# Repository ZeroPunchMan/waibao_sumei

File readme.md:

# 协议说明
校验计算方式: 类型字段和数据字段之和

## 开始或暂停
APP下发:
| 包头  | 方向  | 令牌  | 长度  | 类型  |        数据        | 校验  |
| :---: | :---: | :---: | :---: | :---: | :----------------: | :---: |
| 0xae  | 0x01  | 0xf0  | 0x02  | 0x01  | [0]: 0-暂停;1-开始; | 校验  |

设备回复
| 包头  | 方向  | 令牌  | 长度  | 类型  |        数据        | 校验  |
| :---: | :---: | :---: | :---: | :---: | :----------------: | :---: |
| 0xae  | 0x02  | 0xf0  | 0x02  | 0x01  | [0]: 0-暂停;1-开始;2-电池电量低;3-接入外部电源 | 校验  |

```
开启输出,APP下发内容:
ae 01 f0 02 01 01 02
设备收到后,回复内容:
ae 02 f0 02 01 01 02

如果电池电量低,回复内容:
ae 02 f0 02 01 02 03  
如果接入外部电源,回复内容:
ae 02 f0 02 01 03 04 
```
```
暂停输出,APP下发内容:
ae 01 f0 02 01 00 01
设备收到后,回复内容:
ae 02 f0 02 01 00 01 
```

## 紧急停止
APP下发:
| 包头  | 方向  | 令牌  | 长度  | 类型  | 数据  | 校验  |
| :---: | :---: | :---: | :---: | :---: | :---: | :---: |
| 0xae  | 0x01  | 0xf0  | 0x01  | 0x03  |  无   | 校验  |

设备回复
| 包头  | 方向  | 令牌  | 长度  | 类型  | 数据  | 校验  |
| :---: | :---: | :---: | :---: | :---: | :---: | :---: |
| 0xae  | 0x02  | 0xf0  | 0x01  | 0x03  |  无   | 校验  |

```
紧急停止,APP下发内容:
ae 01 f0 01 03 03
设备收到后,回复内容:
ae 02 f0 01 03 03 
```

## 设置输出
APP下发:
| 包头  | 方向  | 令牌  | 长度  | 类型  |                                                                                      数据                                                                                       | 校验  |
| :---: | :---: | :---: | :---: | :---: | :-----------------------------------------------------------------------------------------------------------------------------------------------------------------------------: | :---: |
| 0xae  | 0x01  | 0xf0  | 0x09  | 0x04  | [0]:手臂电机强度<br> [1]:手臂电机频率<br> [2]:胸部电机强度<br> [3]:胸部电机频率<br> [4]:背面上电机强度<br> [5]:背面上电机频率<br> [6]:背面下电机强度<br> [7]:背面下电机频率<br> | 校验  |

设备回复
| 包头  | 方向  | 令牌  | 长度  | 类型  |                                                                                      数据                                                                                       | 校验  |
| :---: | :---: | :---: | :---: | :---: | :-----------------------------------------------------------------------------------------------------------------------------------------------------------------------------: | :---: |
| 0xae  | 0x02  | 0xf0  | 0x09  | 0x04  | [0]:手臂电机强度<br> [1]:手臂电机频率<br> [2]:胸部电机强度<br> [3]:胸部电机频率<br> [4]:背面上电机强度<br> [5]:背面上电机频率<br> [6]:背面下电机强度<br> [7]:背面下电机频率<br> | 校验  |

```
举例
设置 手臂强度10 频率6; 胸部强度20 频率7; 背面上强度30 频率8; 背面下强度40 频率9; APP下发内容:
ae 01 f0 09 04 0a 06 14 07 1e 08 28 09 86
设备收到后,回复内容:
ae 02 f0 09 04 0a 06 14 07 1e 08 28 09 86 
```

## 电池上报
设备间隔2秒上报电量和电池状态
| 包头  | 方向  | 令牌  | 长度  | 类型  | 数据  | 校验  |
| :---: | :---: | :---: | :---: | :---: | :---: | :---: |
| 0xae  | 0x02  | 0xf0  | 0x03  | 0x05  |  [0]: 电量百分比<br> [1]:电池状态   | 校验  |

电池状态定义如下:
```
1.电量充足
2.电量低
3.充电中
4.充电完成
```

```
举例,电量100,未接入外部电源,设备上报内容如下:
ae 02 f0 03 05 64 01 6a 
```

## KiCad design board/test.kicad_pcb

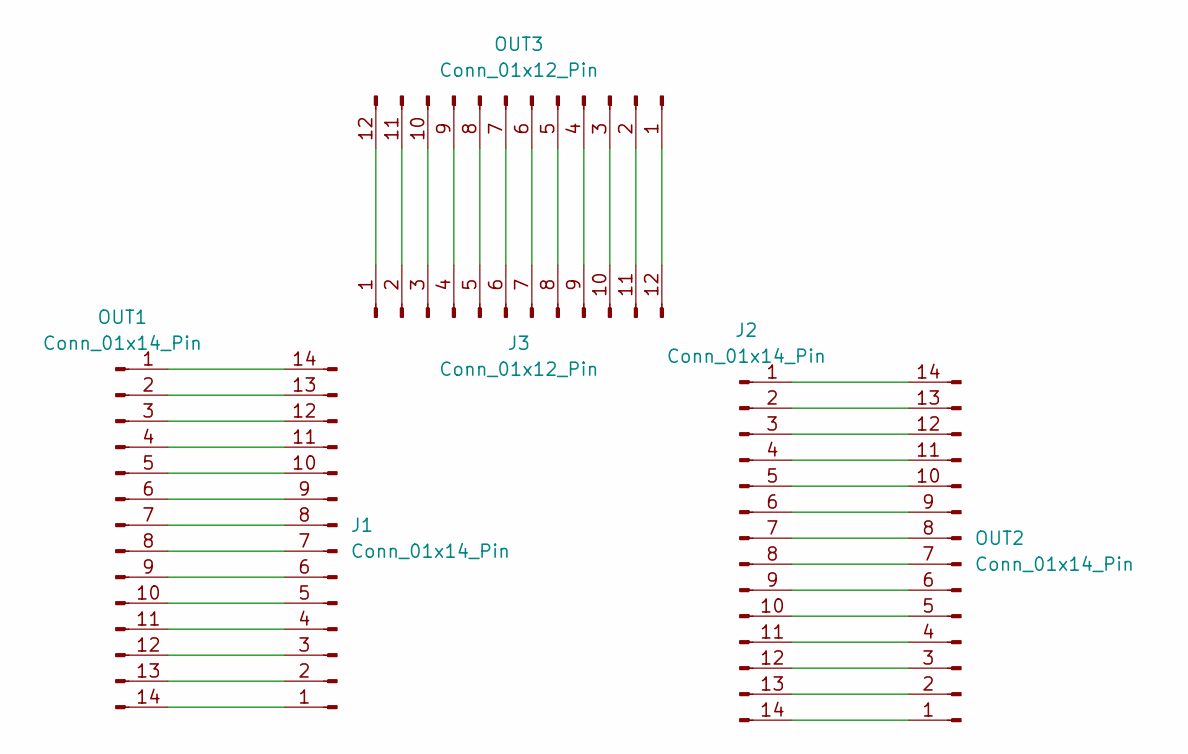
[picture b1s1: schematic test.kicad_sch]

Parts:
J1, J2: Conn_01x14_Pin; PinHeader_1x14_P1.27mm_Vertical
J3: Conn_01x12_Pin; PinHeader_1x12_P1.27mm_Vertical
OUT1, OUT2: Conn_01x14_Pin; PinSocket_1x14_P2.54mm_Vertical
OUT3: Conn_01x12_Pin; PinSocket_1x12_P2.54mm_Vertical

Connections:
unnamed: J1.1, OUT1.14
unnamed: J1.2, OUT1.13
unnamed: J1.3, OUT1.12
unnamed: J1.4, OUT1.11
unnamed: J1.5, OUT1.10
unnamed: J1.6, OUT1.9
unnamed: J1.7, OUT1.8
unnamed: J1.8, OUT1.7
unnamed: J1.9, OUT1.6
unnamed: J1.10, OUT1.5
unnamed: J1.11, OUT1.4
unnamed: J1.12, OUT1.3
unnamed: J1.13, OUT1.2
unnamed: J1.14, OUT1.1
unnamed: J2.1, OUT2.14
unnamed: J2.2, OUT2.13
unnamed: J2.3, OUT2.12
unnamed: J2.4, OUT2.11
unnamed: J2.5, OUT2.10
unnamed: J2.6, OUT2.9
unnamed: J2.7, OUT2.8
unnamed: J2.8, OUT2.7
unnamed: J2.9, OUT2.6
unnamed: J2.10, OUT2.5
unnamed: J2.11, OUT2.4
unnamed: J2.12, OUT2.3
unnamed: J2.13, OUT2.2
unnamed: J2.14, OUT2.1
unnamed: J3.1, OUT3.12
unnamed: J3.2, OUT3.11
unnamed: J3.3, OUT3.10
unnamed: J3.4, OUT3.9
unnamed: J3.5, OUT3.8
unnamed: J3.6, OUT3.7
unnamed: J3.7, OUT3.6
unnamed: J3.8, OUT3.5
unnamed: J3.9, OUT3.4
unnamed: J3.10, OUT3.3
unnamed: J3.11, OUT3.2
unnamed: J3.12, OUT3.1

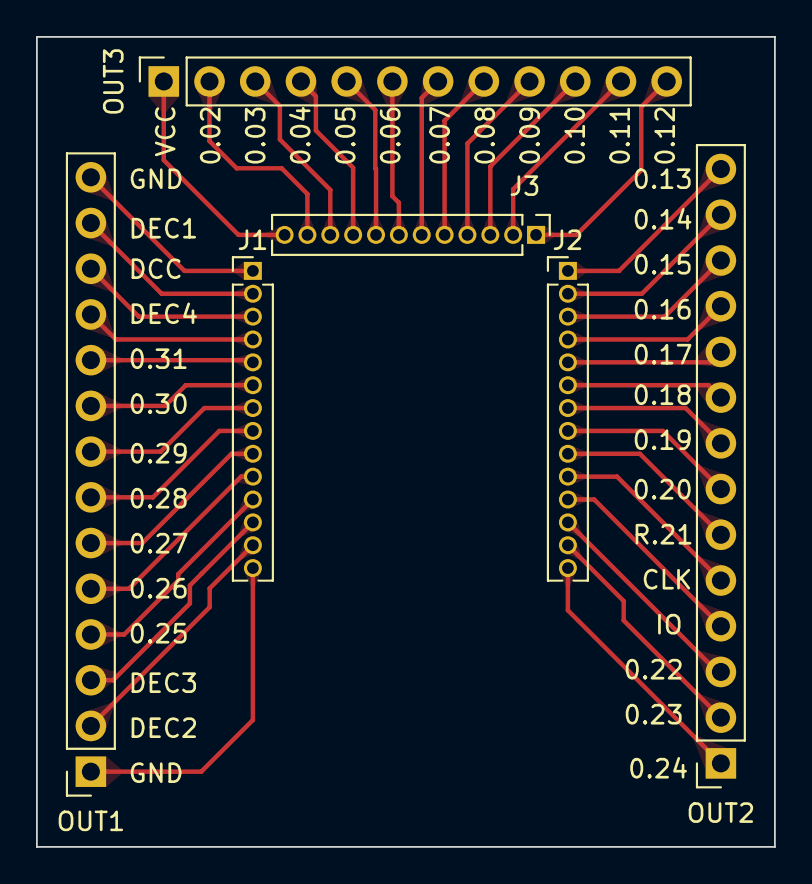
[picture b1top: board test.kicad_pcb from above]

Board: 2 copper layers, 41.0 x 45.0 mm, 6 parts (0 on the bottom side), 40 nets.

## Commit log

2023-11-13 init
2023-11-13 vscode task
2023-11-13 增加批处理
2023-11-14 增加烧录校验
2023-11-16 watch代码移植,编译通过
2023-11-16 烧录运行正常
2023-11-16 协议拆包组包完成,未测试
2023-11-16 版本号通信初步测试ok
2023-11-16 增加测试工具
2023-11-16 增加keil,防止win11下nrf工具不稳定
2023-11-16 keil路径
2023-11-20 增加pwm,未测试
2023-11-20 ADC未测试
2023-11-20 重命名文件
2023-11-21 adc测试ok
2023-11-21 4路mos pwm初步测试ok
2023-11-21 软件模拟led pwm
2023-11-21 提高led pwm速率
2023-11-21 增加部分命令
2023-11-23 输出测试ok
2023-11-23 电量上报测试ok
2023-11-23 toolchain path
2023-11-23 改PWM通道
2023-11-23 todos
2023-11-24 优化电池上报
2023-11-24 电池状态解析
2023-11-28 修改完成,未测试
2023-11-28 初步测试ok
2023-11-28 强度0关闭输出
2023-11-28 增加协议文档
2023-11-28 电量改为过去1秒最大adc值,未测试
2023-12-02 ble name
2023-12-08 修改IO
2023-12-08 修改ADC
2023-12-08 改完,未测试
2023-12-08 增加呼吸灯频率处理
2023-12-08 测试底板,画了符号
2023-12-08 用排针封装拼凑
2023-12-08 开发板调试通过
2023-12-08 测试通过
2023-12-08 协议文档修改
2023-12-09 修改输出逻辑，未测试
2023-12-10 修改波形
2023-12-10 版本号V3
2023-12-24 电量优化，断蓝牙关输出
2023-12-24 关输出加日志
2023-12-25 电池电量改为5阶段,还需充电修正
2023-12-25 模式2全开
2023-12-25 调整电压参数
2023-12-26 充电电压修正
2023-12-26 电池adc加滤波
2023-12-26 增加softdevice
2023-12-26 adc滤波采样次数增加
2023-12-26 adc滤波溢出问题
2023-12-26 调整档位电压
